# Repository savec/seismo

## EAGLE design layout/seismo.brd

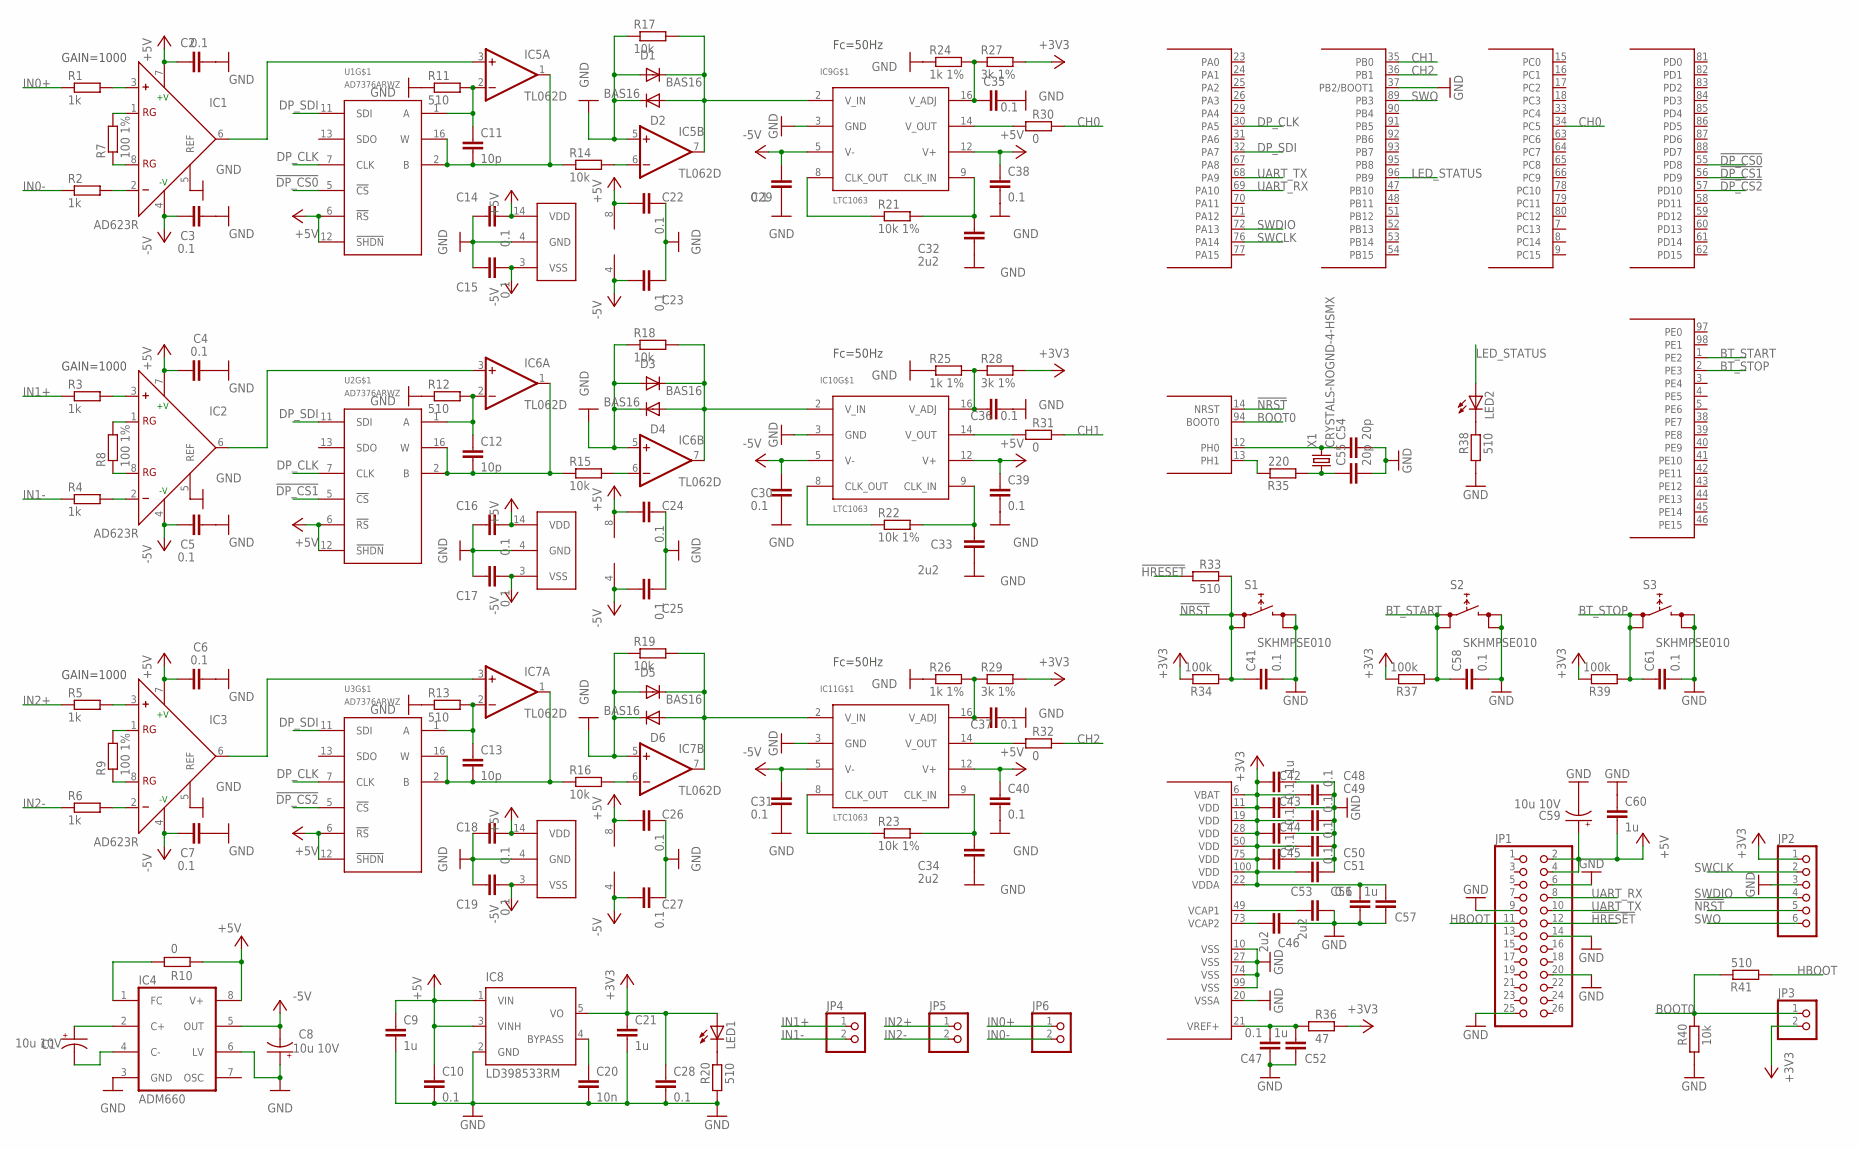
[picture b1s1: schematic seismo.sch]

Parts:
C1, C8, C59: 10u 10V; SMC_A
C2, C3, C4, C5, C6, C7, C10, C14, C15, C16, C17, C18, C19, C22, C23, C24, C25, C26, C27, C28, C29, C30, C31, C35, C36, C37, C38, C39, C40, C41, C43, C44, C45, C47, C48, C49, C50, C51, C56, C58, C61: 0.1; C0805
C9, C21, C42, C52, C57, C60: 1u; C0805
C11, C12, C13: 10p; C0805
C20: 10n; C0805
C32, C33, C34, C46, C53: 2u2; C0805
C54, C55: 20p; C0805
D1, D2, D3, D4, D5, D6: BAS16; SOT23
IC1, IC2, IC3: AD623R; SO8
IC4: ADM660; SO8
IC5, IC6, IC7: TL062D; SO08
IC8: LD398533RM; SOT23-5L
IC9, IC10, IC11: LTC1063; SOIC127P1032X264-16N
JP1: PINHD-2X13; 2X13
JP2: PINHD-1X6; 1X06
JP3, JP4, JP5, JP6: PINHD-1X2; 1X02
LED1, LED2: LEDCHIPLED_1206; CHIPLED_1206
R1, R2, R3, R4, R5, R6: 1k; R0805W
R7, R8, R9: 100 1%; R0805W
R10, R30, R31, R32: 0; R0805W
R11, R12, R13, R20, R33, R38, R41: 510; R0805W
R14, R15, R16, R17, R18, R19, R40: 10k; R0805W
R21, R22, R23: 10k 1%; R0805W
R24, R25, R26: 1k 1%; R0805W
R27, R28, R29: 3k 1%; R0805W
R34, R37, R39: 100k; R0805W
R35: 220; R0805W
R36: 47; R0805W
S1, S2, S3: SKHMPSE010; SKHMPXE010
U1, U2, U3: AD7376ARWZ; SO-16W
U4: STM32F4-100; SQFP-S-14X14-100
X1: CRYSTALS-NOGND-4-HSMX; HC49-4-HSMX

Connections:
!DP_CS0: U1.5 (!CS), U4.55 (PD8)
!DP_CS1: U2.5 (!CS), U4.56 (PD9)
!DP_CS2: U3.5 (!CS), U4.57 (PD10)
!HRESET: JP1.12, R33.1
!NRST: C41.1, JP2.5, R33.2, R34.1, S1.1 (1.1), S1.2 (1.2), U4.14 (NRST)
+3V3: C21.1, C28.1, C42.1, C43.1, C44.1, C45.1, C48.1, C49.1, C50.1, C51.1, C56.2, C57.2, IC8.5 (VO), JP2.1, JP3.2, LED1.A, R27.2, R28.2, R29.2, R34.2, R36.2, R37.2, R39.2, U4.6 (VBAT), U4.11 (VDD), U4.19 (VDD), U4.22 (VDDA), U4.28 (VDD), U4.50 (VDD), U4.75 (VDD), U4.100 (VDD)
+5V: C2.1, C4.1, C6.1, C9.1, C10.1, C14.2, C16.2, C18.2, C22.1, C24.1, C26.1, C38.1, C39.1, C40.1, C59.+, C60.2, IC1.7 (+V), IC2.7 (+V), IC3.7 (+V), IC4.8 (V+), IC5.8 (V+), IC6.8 (V+), IC7.8 (V+), IC8.1 (VIN), IC8.3 (VINH), IC9.12 (V+), IC10.12 (V+), IC11.12 (V+), JP1.2, JP1.4, R10.2, U1.6 (!RS), U1.12 (!SHDN), U1.14 (VDD), U2.6 (!RS), U2.12 (!SHDN), U2.14 (VDD), U3.6 (!RS), U3.12 (!SHDN), U3.14 (VDD)
-5V: C3.1, C5.1, C7.1, C8.-, C15.2, C17.2, C19.2, C23.1, C25.1, C27.1, C29.1, C30.1, C31.1, IC1.4 (-V), IC2.4 (-V), IC3.4 (-V), IC4.5 (OUT), IC5.4 (V-), IC6.4 (V-), IC7.4 (V-), IC9.5 (V-), IC10.5 (V-), IC11.5 (V-), U1.3 (VSS), U2.3 (VSS), U3.3 (VSS)
BOOT0: JP3.1, R40.2, R41.2, U4.94 (BOOT0)
BT_START: C58.1, R37.1, S2.1 (1.1), S2.2 (1.2), U4.1 (PE2)
BT_STOP: C61.1, R39.1, S3.1 (1.1), S3.2 (1.2), U4.2 (PE3)
CH0: R30.2, U4.34 (PC5)
CH1: R31.2, U4.35 (PB0)
CH2: R32.2, U4.36 (PB1)
DP_CLK: U1.7 (CLK), U2.7 (CLK), U3.7 (CLK), U4.30 (PA5)
DP_SDI: U1.11 (SDI), U2.11 (SDI), U3.11 (SDI), U4.32 (PA7)
GND: C2.2, C3.2, C4.2, C5.2, C6.2, C7.2, C8.+, C9.2, C10.2, C14.1, C15.1, C16.1, C17.1, C18.1, C19.1, C20.2, C21.2, C22.2, C23.2, C24.2, C25.2, C26.2, C27.2, C28.2, C29.2, C30.2, C31.2, C32.2, C33.2, C34.2, C35.2, C36.2, C37.2, C38.2, C39.2, C40.2, C41.2, C42.2, C43.2, C44.2, C45.2, C46.1, C47.1, C48.2, C49.2, C50.2, C51.2, C52.1, C53.1, C54.2, C55.2, C56.1, C57.1, C58.2, C59.-, C60.1, C61.2, D1.1 (A), D2.3 (C), D3.1 (A), D4.3 (C), D5.1 (A), D6.3 (C), IC1.5 (REF), IC2.5 (REF), IC3.5 (REF), IC4.3 (GND), IC4.6 (LV), IC5.5 (+IN), IC6.5 (+IN), IC7.5 (+IN), IC8.2 (GND), IC9.3 (GND), IC10.3 (GND), IC11.3 (GND), JP1.6, JP1.9, JP1.14, JP1.20, JP1.25, JP2.3, R11.1, R12.1, R13.1, R17.1, R18.1, R19.1, R20.1, R24.1, R25.1, R26.1, R38.1, R40.1, S1.3 (2.1), S1.4 (2.2), S2.3 (2.1), S2.4 (2.2), S3.3 (2.1), S3.4 (2.2), U1.4 (GND), U2.4 (GND), U3.4 (GND), U4.10 (VSS), U4.20 (VSSA), U4.27 (VSS), U4.37 (PB2/BOOT1), U4.74 (VSS), U4.99 (VSS)
HBOOT: JP1.11, R41.1
IN0+: JP6.1, R1.1
IN0-: JP6.2, R2.1
IN1+: JP4.1, R3.1
IN1-: JP4.2, R4.1
IN2+: JP5.1, R5.1
IN2-: JP5.2, R6.1
LED_STATUS: LED2.A, U4.96 (PB9)
unnamed: IC1.2 (-), R2.2
unnamed: IC1.8 (RG), R7.1
unnamed: IC1.1 (RG), R7.2
unnamed: IC1.3 (+), R1.2
unnamed: C55.1, R35.1, X1.1
unnamed: IC9.8 (CLK_OUT), R21.1
unnamed: C32.1, IC9.9 (CLK_IN), R21.2
unnamed: C35.1, IC9.16 (V_ADJ), R24.2, R27.1
unnamed: R35.2, U4.13 (PH1)
unnamed: IC9.14 (V_OUT), R30.1
unnamed: C1.+, IC4.2 (C+)
unnamed: IC10.8 (CLK_OUT), R22.1
unnamed: C33.1, IC10.9 (CLK_IN), R22.2
unnamed: IC2.2 (-), R4.2
unnamed: IC2.8 (RG), R8.1
unnamed: IC2.1 (RG), R8.2
unnamed: IC2.3 (+), R3.2
unnamed: C36.1, IC10.16 (V_ADJ), R25.2, R28.1
unnamed: IC10.14 (V_OUT), R31.1
unnamed: C1.-, IC4.4 (C-)
unnamed: C53.2, U4.49 (VCAP1)
unnamed: IC11.8 (CLK_OUT), R23.1
unnamed: C34.1, IC11.9 (CLK_IN), R23.2
unnamed: IC3.2 (-), R6.2
unnamed: IC3.8 (RG), R9.1
unnamed: IC3.1 (RG), R9.2
unnamed: IC3.3 (+), R5.2
unnamed: C37.1, IC11.16 (V_ADJ), R26.2, R29.1
unnamed: IC11.14 (V_OUT), R32.1
unnamed: IC4.1 (FC), R10.1
unnamed: C11.2, IC5.1 (OUT), R14.1, U1.2 (B), U1.16 (W)
unnamed: IC1.6 (OUT), IC5.3 (+IN)
unnamed: C11.1, IC5.2 (-IN), R11.2, U1.1 (A)
unnamed: IC5.6 (-IN), R14.2
unnamed: C20.1, IC8.4 (BYPASS)
unnamed: D1.3 (C), D2.1 (A), IC5.7 (OUT), IC9.2 (V_IN), R17.2
unnamed: C46.2, U4.73 (VCAP2)
unnamed: C12.2, IC6.1 (OUT), R15.1, U2.2 (B), U2.16 (W)
unnamed: IC2.6 (OUT), IC6.3 (+IN)
unnamed: C12.1, IC6.2 (-IN), R12.2, U2.1 (A)
unnamed: IC6.6 (-IN), R15.2
unnamed: D3.3 (C), D4.1 (A), IC6.7 (OUT), IC10.2 (V_IN), R18.2
unnamed: C13.2, IC7.1 (OUT), R16.1, U3.2 (B), U3.16 (W)
unnamed: IC3.6 (OUT), IC7.3 (+IN)
unnamed: C13.1, IC7.2 (-IN), R13.2, U3.1 (A)
unnamed: IC7.6 (-IN), R16.2
unnamed: D5.3 (C), D6.1 (A), IC7.7 (OUT), IC11.2 (V_IN), R19.2
unnamed: C54.1, U4.12 (PH0), X1.2
unnamed: LED1.C, R20.2
unnamed: LED2.C, R38.2
SWCLK: JP2.2, U4.76 (PA14)
SWDIO: JP2.4, U4.72 (PA13)
SWO: JP2.6, U4.89 (PB3)
UART_RX: JP1.8, U4.69 (PA10)
UART_TX: JP1.10, U4.68 (PA9)
VREF: C47.2, C52.2, R36.1, U4.21 (VREF+)

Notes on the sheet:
GAIN=1000
Fc=50Hz

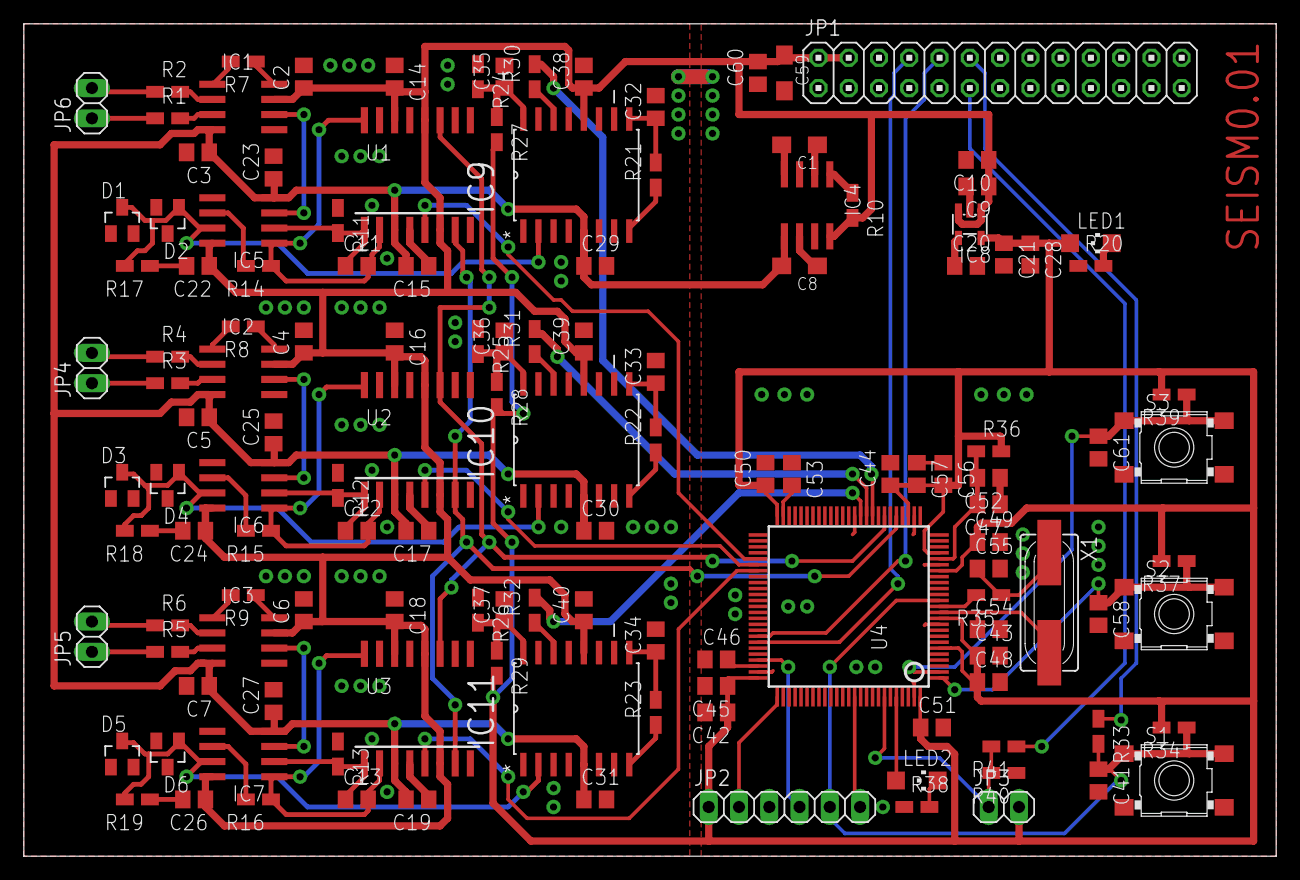
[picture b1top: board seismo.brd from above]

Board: 2 copper layers, 105.1 x 69.8 mm, 135 parts (0 on the bottom side), 81 nets.

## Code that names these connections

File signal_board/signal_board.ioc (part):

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Mcu.Name=STM32F407V(E-G)Tx
Mcu.Package=LQFP100
Mcu.UserName=STM32F407VGTx
PA10.Mode=Asynchronous
PA10.Signal=USART1_RX
PA13.Mode=Trace-Asynchronous_SW
PA13.Signal=SYS_JTMS-SWDIO
PA14.Mode=Trace-Asynchronous_SW
PA14.Signal=SYS_JTCK-SWCLK
PA5.Mode=TX_Only_Simplex_Unidirect_Master
PA5.Signal=SPI1_SCK
PA7.Mode=TX_Only_Simplex_Unidirect_Master
PA7.Signal=SPI1_MOSI
PA9.Mode=Asynchronous
PA9.Signal=USART1_TX
PB0.Signal=ADCx_IN8
PB1.Signal=ADCx_IN9
PB3.Mode=Trace-Asynchronous_SW
PB3.Signal=SYS_JTDO-SWO
PB9.Signal=GPIO_Output
PC5.Signal=ADCx_IN15
PD10.Signal=GPIO_Output
PD8.Signal=GPIO_Output
PD9.Signal=GPIO_Output
PE2.Signal=GPIO_Input
PE3.Signal=GPIO_Input
PH0-OSC_IN.Mode=HSE-External-Oscillator
PH0-OSC_IN.Signal=RCC_OSC_IN
PH1-OSC_OUT.Mode=HSE-External-Oscillator
PH1-OSC_OUT.Signal=RCC_OSC_OUT
RCC.HSE_VALUE=8000000
RCC.SYSCLKFreq_VALUE=168000000
RCC.SYSCLKSource=RCC_SYSCLKSOURCE_PLLCLK

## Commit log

2015-05-20 cleaning
2015-05-21 stlink symlinks
2015-05-25 build system & debug modified
2015-05-27 adc channels & tim
2015-05-27 prepare to launch adc
2015-05-27 adc clock divider
2015-05-29 some experiments
2015-06-12 hw keys; migrate to freertos 8.2
2015-06-13 ad7376 testing
2015-06-13 usart tx dma
2015-06-13 packet sending over dma
2015-06-14 byte stuffing synchronization; rx state machine
2015-06-14 packets unstuffing; bugs fixed
2015-06-14 dsp task
2015-06-15 fir realisation; global config; start/stop acquire
2015-06-15 main programm logic
2015-06-15 channel data tx
